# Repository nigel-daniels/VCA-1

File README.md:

# VCA 1

This dual VCA AS2164 VCA is based on the Hagiwo's [Dual VCA Rev.2](https://note.com/solder_state/n/nd82c027d0597). 

To calibrate the range for each VCA (Where *n* is the VCA number) using the test points[^1]:

1. Set the Offset pot to be closed. Now measure at CV*n* and ensure it is at 0V, now measure at OUT*n* and adjust the 100k (104) trim pot until the output is 0.
2. Still with the Offset pot closed, measure CV*n* and ensure it is at 5V, now check the IN*n* V and record it, next measure OUT*n* and adjust the 10K (103) trimpot and ensure the OUT*n* V == IN*n* V[^2]. NB: You can set it to more or less if you like but less than x0.1 or more than x5 makes the VCA hard to use.

[^1]: Don't forget to plug a jack in the OUT*n* socket or it will be connected to GND.
[^2]: This could be the inverse of the IN*n* V i.e. -V.

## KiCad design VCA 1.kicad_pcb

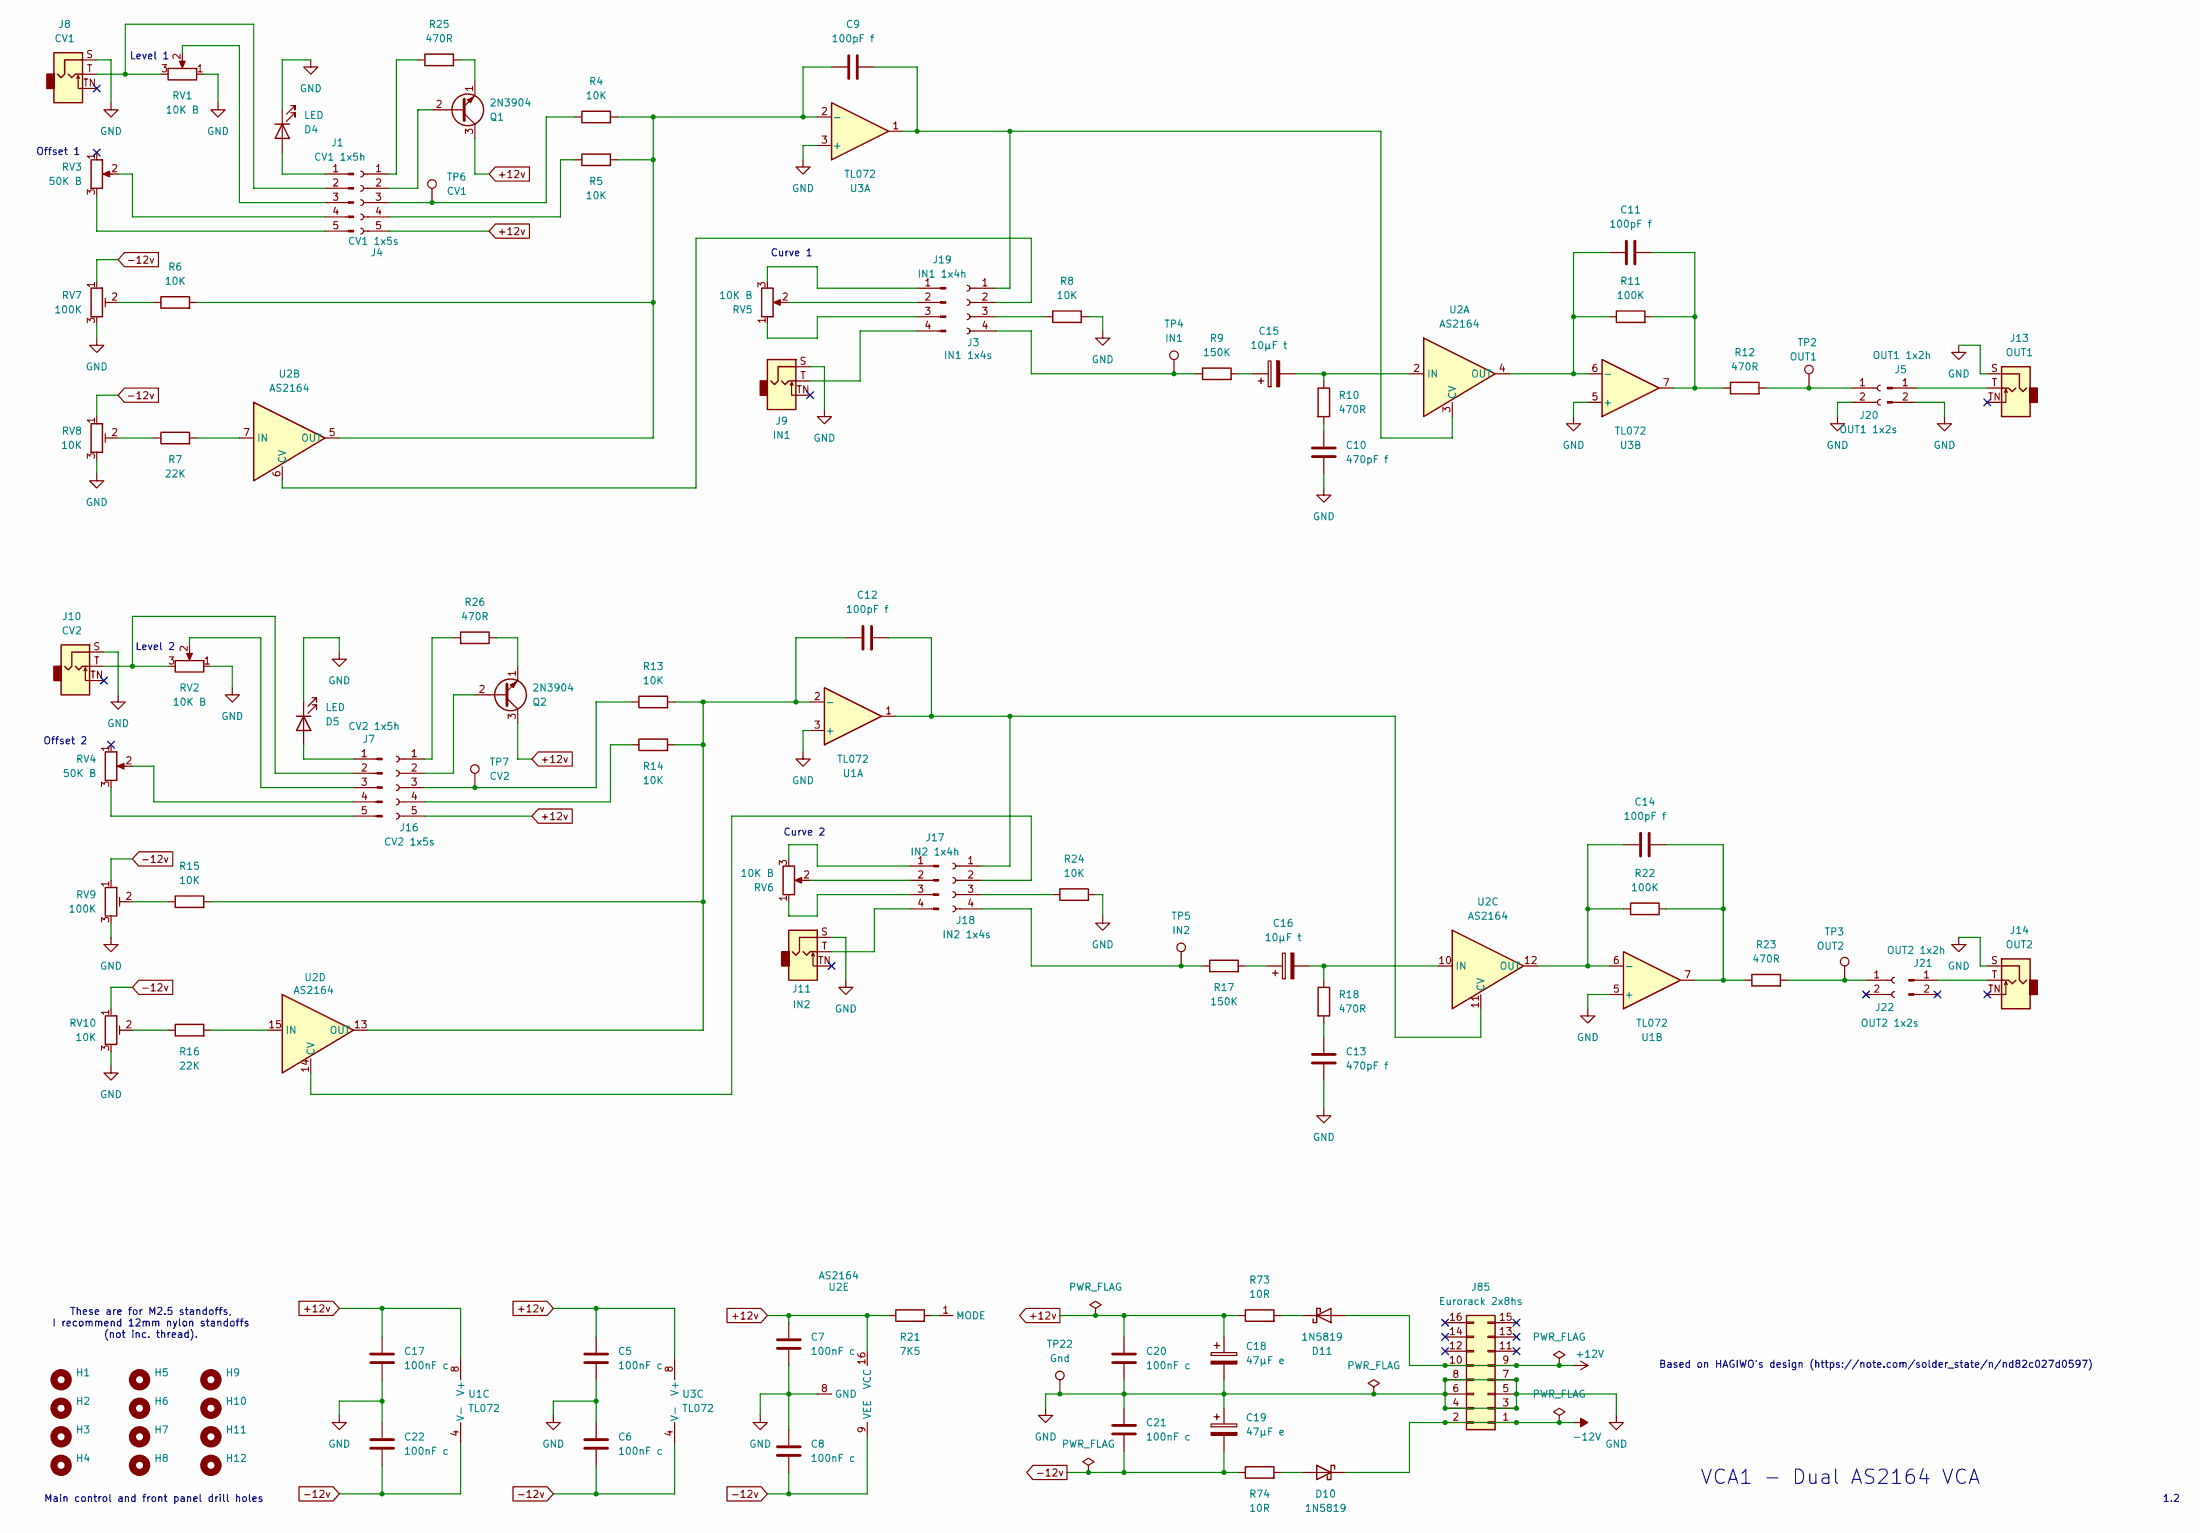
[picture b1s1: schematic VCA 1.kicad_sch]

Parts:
C5, C6, C7, C8, C17, C20, C21, C22: 100nF c; C_Disc_D4.7mm_W2.5mm_P5.00mm
C9, C11, C12, C14: 100pF f; C_Rect_L7.2mm_W2.5mm_P5.00mm
C10, C13: 470pF f; C_Rect_L7.2mm_W2.5mm_P5.00mm
C15, C16: 10μF t; CP_Radial_Tantal_D4.5mm_P2.50mm
C18, C19: 47μF e; CP_Radial_D5.0mm_P2.50mm
D4, D5: LED; LED_D3.0mm_FlatTop
D10, D11: 1N5819; D_DO-41_SOD81_P10.16mm_Horizontal
H1, H2, H3, H4, H5, H6, H7, H8: MountingHole_2.7mm_M2.5
H9, H10, H11, H12: MountingHole_3.2mm_M3
J1: CV1 1x5h; PinHeader_1x05_P2.54mm_Vertical
J3: IN1 1x4s; PinSocket_1x04_P2.54mm_Vertical
J4: CV1 1x5s; PinSocket_1x05_P2.54mm_Vertical
J5: OUT1 1x2h; PinHeader_1x02_P2.54mm_Vertical
J7: CV2 1x5h; PinHeader_1x05_P2.54mm_Vertical
J8: CV1; Jack_3.5mm_QingPu_WQP-PJ398SM_Vertical_CircularHoles
J9: IN1; Jack_3.5mm_QingPu_WQP-PJ398SM_Vertical_CircularHoles
J10: CV2; Jack_3.5mm_QingPu_WQP-PJ398SM_Vertical_CircularHoles
J11: IN2; Jack_3.5mm_QingPu_WQP-PJ398SM_Vertical_CircularHoles
J13: OUT1; Jack_3.5mm_QingPu_WQP-PJ398SM_Vertical_CircularHoles
J14: OUT2; Jack_3.5mm_QingPu_WQP-PJ398SM_Vertical_CircularHoles
J16: CV2 1x5s; PinSocket_1x05_P2.54mm_Vertical
J17: IN2 1x4h; PinHeader_1x04_P2.54mm_Vertical
J18: IN2 1x4s; PinSocket_1x04_P2.54mm_Vertical
J19: IN1 1x4h; PinHeader_1x04_P2.54mm_Vertical
J20: OUT1 1x2s; PinSocket_1x02_P2.54mm_Vertical
J21: OUT2 1x2h; PinHeader_1x02_P2.54mm_Vertical
J22: OUT2 1x2s; PinSocket_1x02_P2.54mm_Vertical
J85: Eurorack 2x8hs; IDC-Header_2x08_P2.54mm_Vertical
Q1, Q2: 2N3904; TO-92_Inline_Wide
R4, R5, R8, R24: 10K; R_Axial_DIN0204_L3.6mm_D1.6mm_P2.54mm_Vertical
R6, R13, R14, R15: 10K; R_Axial_DIN0204_L3.6mm_D1.6mm_P7.62mm_Horizontal
R7, R16: 22K; R_Axial_DIN0204_L3.6mm_D1.6mm_P7.62mm_Horizontal
R9: 150K; R_Axial_DIN0204_L3.6mm_D1.6mm_P7.62mm_Horizontal
R10, R18, R25: 470R; R_Axial_DIN0204_L3.6mm_D1.6mm_P2.54mm_Vertical
R11, R22: 100K; R_Axial_DIN0204_L3.6mm_D1.6mm_P2.54mm_Vertical
R12, R23, R26: 470R; R_Axial_DIN0204_L3.6mm_D1.6mm_P7.62mm_Horizontal
R17: 150K; R_Axial_DIN0204_L3.6mm_D1.6mm_P2.54mm_Vertical
R21: 7K5; R_Axial_DIN0204_L3.6mm_D1.6mm_P7.62mm_Horizontal
R73, R74: 10R; R_Axial_DIN0204_L3.6mm_D1.6mm_P2.54mm_Vertical
RV1, RV2, RV5, RV6: 10K B; Potentiometer_Alps_RK09L_Single_Vertical
RV3, RV4: 50K B; Potentiometer_Alps_RK09L_Single_Vertical
RV7, RV9: 100K; Potentiometer_Bourns_3296X_Horizontal
RV8, RV10: 10K; Potentiometer_Bourns_3296X_Horizontal
TP2: OUT1; TestPoint_Loop_D2.50mm_Drill1.0mm
TP3: OUT2; TestPoint_Loop_D2.50mm_Drill1.0mm
TP4: IN1; TestPoint_Loop_D2.50mm_Drill1.0mm
TP5: IN2; TestPoint_Loop_D2.50mm_Drill1.0mm
TP6: CV1; TestPoint_Loop_D2.50mm_Drill1.0mm
TP7: CV2; TestPoint_Loop_D2.50mm_Drill1.0mm
TP22: Gnd; TestPoint_Loop_D2.50mm_Drill1.0mm
U1, U3: TL072; DIP-8_W7.62mm_Socket
U2: AS2164; DIP-16_W7.62mm_Socket

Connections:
+12V: D11.2 (A), J85.9, J85.10
+12v: C5.1, C7.1, C17.1, C18.1, C20.1, J4.5, J16.5, Q1.3 (C), Q2.3 (C), R21.1, R73.1, U1.8 (V+), U2.16 (VCC), U3.8 (V+)
-12V: D10.1 (K), J85.1, J85.2
-12v: C6.2, C8.2, C19.2, C21.2, C22.2, R74.1, RV7.1, RV8.1, RV9.1, RV10.1, U1.4 (V-), U2.9 (VEE), U3.4 (V-)
GND: C5.2, C6.1, C7.2, C8.1, C10.2, C13.2, C17.2, C18.2, C19.1, C20.2, C21.1, C22.1, D4.1 (K), D5.1 (K), J5.2, J8.S, J9.S, J10.S, J11.S, J13.S, J14.S, J20.2, J85.3, J85.4, J85.5, J85.6, J85.7, J85.8, R8.2, R24.2, RV1.1, RV2.1, RV7.3, RV8.3, RV9.3, RV10.3, TP22.1 (1_1), U1.3 (+), U1.5 (+), U2.8 (GND), U3.3 (+), U3.5 (+)
unnamed: C10.1, R10.2
unnamed: C11.2, R11.2, R12.1, U3.7
unnamed: C13.1, R18.2
unnamed: C14.2, R22.2, R23.1, U1.7
unnamed: C15.1, R9.2
unnamed: C16.1, R17.2
unnamed: D4.2 (A), J1.1
unnamed: D5.2 (A), J7.1
unnamed: D10.2 (A), R74.2
unnamed: D11.1 (K), R73.2
unnamed: J1.2, J8.T, RV1.3
unnamed: J1.3, RV1.2
unnamed: J1.4, RV3.2
unnamed: J1.5, RV3.3
unnamed: C9.2, J3.1, U2.3 (CV), U3.1
unnamed: J3.2, U2.6 (CV)
unnamed: J3.3, R8.1
unnamed: J3.4, R9.1, TP4.1 (1_1)
unnamed: J4.1, R25.1
unnamed: J4.2, Q1.2 (B)
unnamed: J4.3, R4.1, TP6.1 (1_1)
unnamed: J4.4, R5.1
unnamed: J5.1, J13.T
unnamed: J7.2, J10.T, RV2.3
unnamed: J7.3, RV2.2
unnamed: J7.4, RV4.2
unnamed: J7.5, RV4.3
unnamed: J16.1, R26.2
unnamed: J16.2, Q2.2 (B)
unnamed: J16.3, R13.1, TP7.1 (1_1)
unnamed: J16.4, R14.1
unnamed: J17.1, RV6.3
unnamed: J17.2, RV6.2
unnamed: J17.3, RV6.1
unnamed: J11.T, J17.4
unnamed: C12.2, J18.1, U1.1, U2.11 (CV)
unnamed: J18.2, U2.14 (CV)
unnamed: J18.3, R24.1
unnamed: J18.4, R17.1, TP5.1 (1_1)
unnamed: J19.1, RV5.3
unnamed: J19.2, RV5.2
unnamed: J19.3, RV5.1
unnamed: J9.T, J19.4
unnamed: J20.1, R12.2, TP2.1 (1_1)
unnamed: J14.T, J21.1 (Pin_1_1)
unnamed: J22.1 (Pin_1_1), R23.2, TP3.1 (1_1)
unnamed: Q1.1 (E), R25.2
unnamed: Q2.1 (E), R26.1
unnamed: R6.1, RV7.2
unnamed: R7.1, RV8.2
unnamed: R15.1, RV9.2
unnamed: R16.1, RV10.2
unnamed: C12.1, R13.2, R14.2, R15.2, U1.2 (-), U2.13 (OUT)
unnamed: C14.1, R22.1, U1.6 (-), U2.12 (OUT)
unnamed: C15.2, R10.1, U2.2 (IN)
unnamed: C11.1, R11.1, U2.4 (OUT), U3.6 (-)
unnamed: R7.2, U2.7 (IN)
unnamed: C9.1, R4.2, R5.2, R6.2, U2.5 (OUT), U3.2 (-)
unnamed: C16.2, R18.1, U2.10 (IN)
unnamed: R16.2, U2.15 (IN)
unnamed: R21.2, U2.1 (MODE)

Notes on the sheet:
Curve 2
Level 1
Offset 1
Main control and front panel drill holes
These are for M2.5 standoffs, I recommend 12mm nylon standoffs (not inc. thread).
1.2
Offset 2
Based on HAGIWO's design (https://note.com/solder_state/n/nd82c027d0597)
Curve 1
VCA1 - Dual AS2164 VCA
Level 2

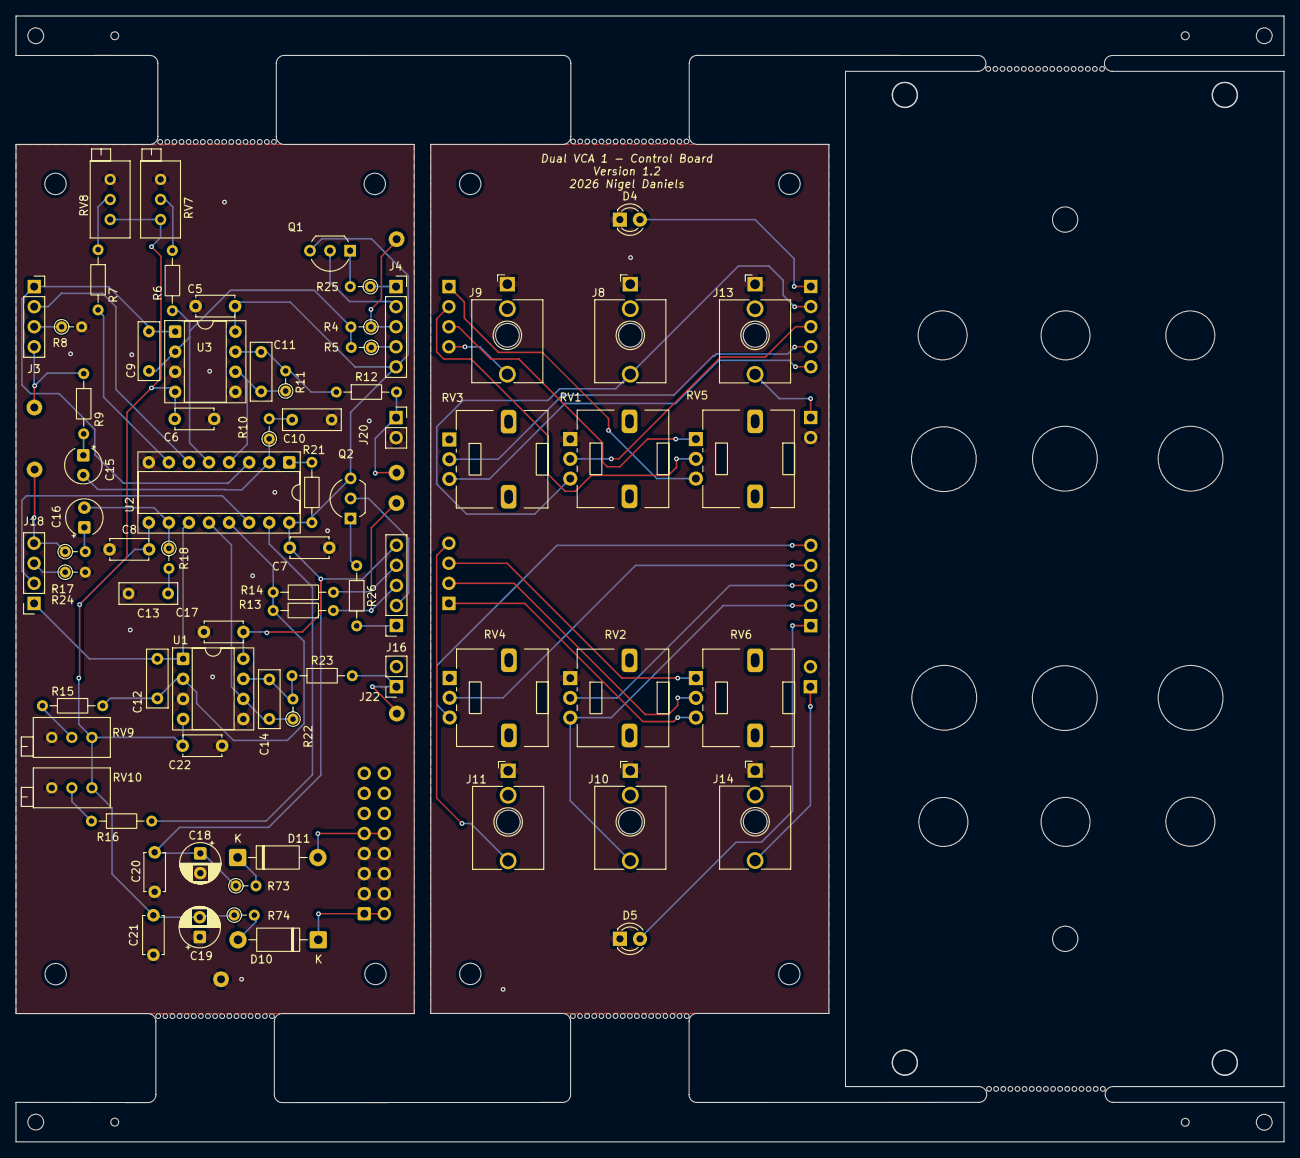
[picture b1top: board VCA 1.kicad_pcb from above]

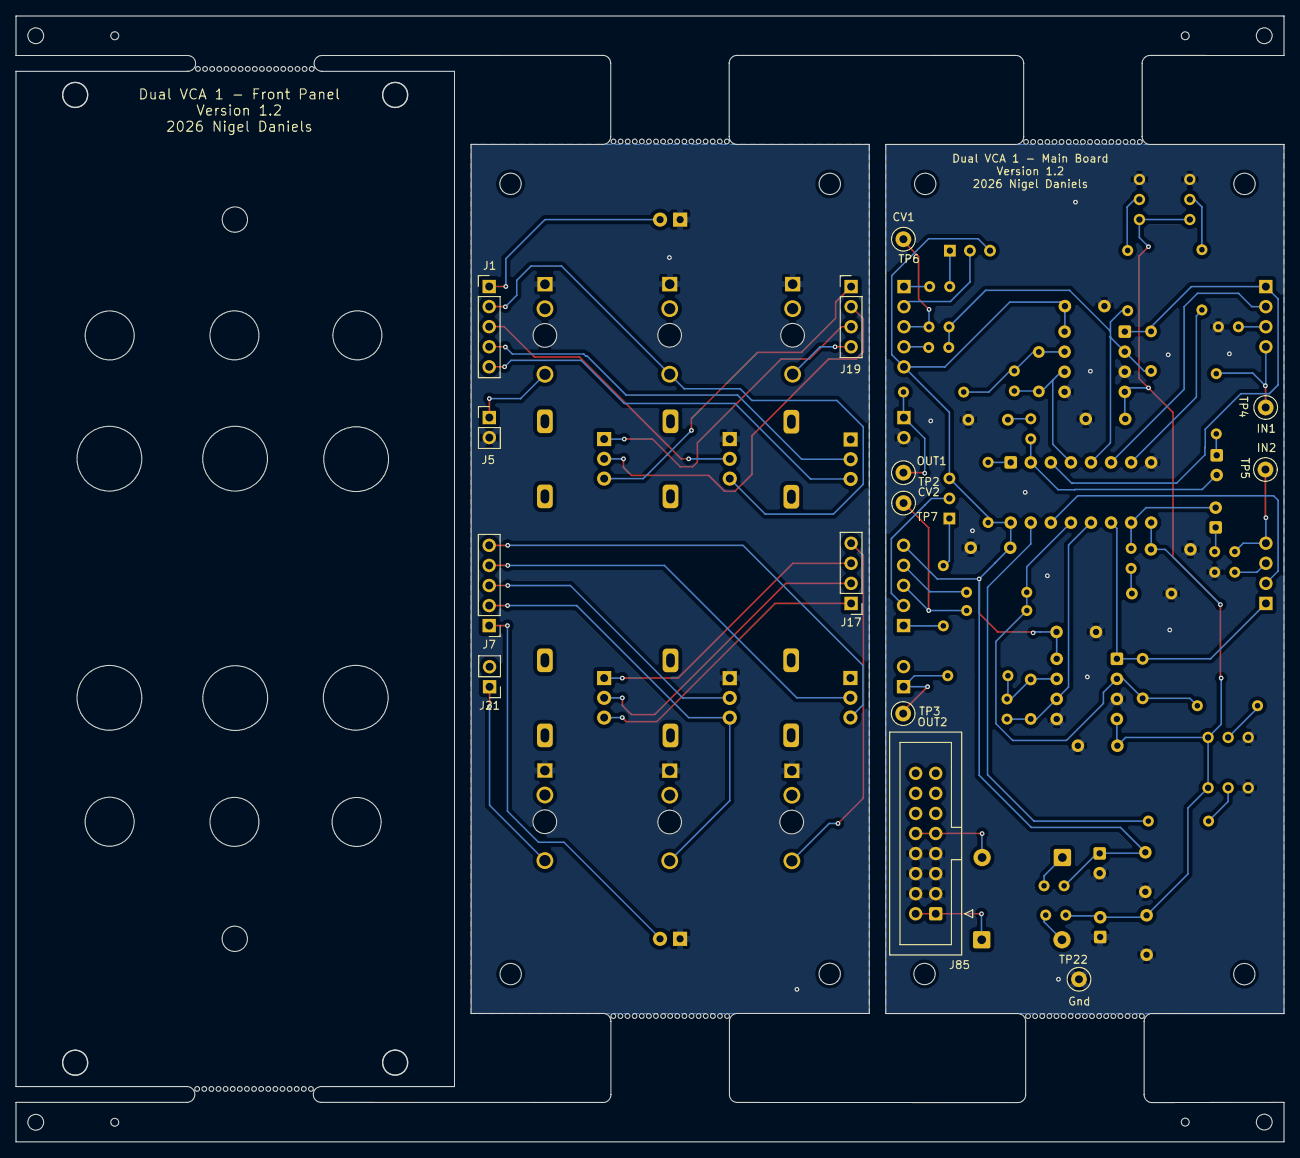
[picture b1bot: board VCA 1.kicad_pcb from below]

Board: 2 copper layers, 160.4 x 142.4 mm, 98 parts (14 on the bottom side), 66 nets.

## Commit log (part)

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2026-04-06 fixed readme
2026-04-27 Updated schematic and .gitignore
2026-06-09 Added input LED
2026-06-12 Added test points and calibration information.
2026-06-16 Started on the PCB layout
2026-06-16 PCB passes EDC and panel cutouts done
2026-06-16 Connected ground islands
2026-06-17 Updated to use CNC constraints
2026-06-17 Rotated PCB for CNC use
2026-06-18 Updated edge cuts for Flatcam
2026-06-20 Updated vias and reoriented design.
